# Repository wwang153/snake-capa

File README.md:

# snake-capa
 This is the sub directory for BIGSS Snake Tool ROS2 Description.

Access Link below:

https://github.com/jhu-bigss/CDM_Capacitive_Shape_Sensing_ROS2

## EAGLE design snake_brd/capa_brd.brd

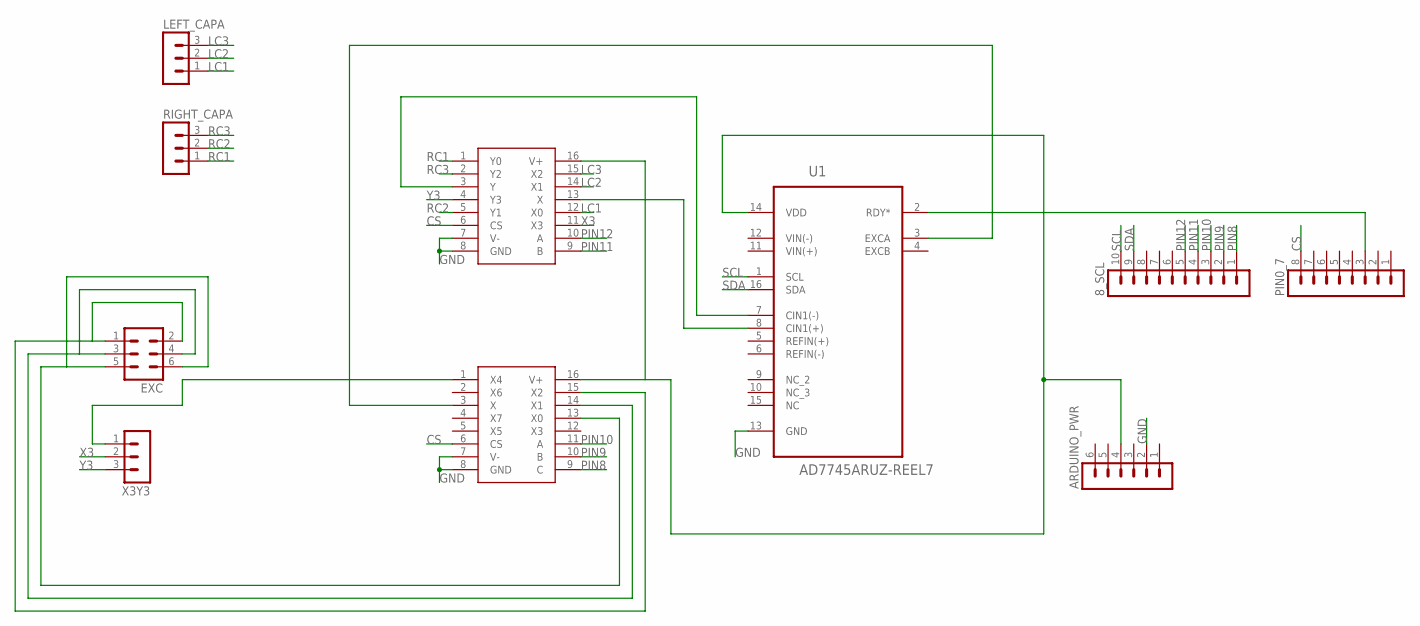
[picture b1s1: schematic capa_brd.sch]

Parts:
8_SCL: MA10-1
ARDUINO_PWR: MA06-1
EXC: MA03-2
LEFT_CAPA: MA03-1
PIN0_7: MA08-1
RIGHT_CAPA: MA03-1
U1: AD7745ARUZ-REEL7; SOP65P640X120-16N
U$1: DG4051E
U$2: DG4052E
X3Y3: MA03-1

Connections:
CS: PIN0_7.8, U$1.6 (CS), U$2.6 (CS)
GND: ARDUINO_PWR.2, U1.13 (GND), U$1.7 (V-), U$1.8 (GND), U$2.7 (V-), U$2.8 (GND)
LC1: LEFT_CAPA.1, U$2.12 (X0)
LC2: LEFT_CAPA.2, U$2.14 (X1)
LC3: LEFT_CAPA.3, U$2.15 (X2)
unnamed: U1.8 (CIN1(+)), U$2.13 (X)
unnamed: U1.7 (CIN1(-)), U$2.3 (Y)
unnamed: U1.3 (EXCA), U$1.3 (X)
unnamed: EXC.5, EXC.6, U$1.13 (X0)
unnamed: EXC.3, EXC.4, U$1.14 (X1)
unnamed: EXC.1, EXC.2, U$1.15 (X2)
unnamed: PIN0_7.3, U1.2 (RDY*)
unnamed: ARDUINO_PWR.4, U1.14 (VDD), U$1.16 (V+), U$2.16 (V+)
unnamed: U$1.1 (X4), X3Y3.1
PIN8: 8_SCL.1, U$1.9 (C)
PIN9: 8_SCL.2, U$1.10 (B)
PIN10: 8_SCL.3, U$1.11 (A)
PIN11: 8_SCL.4, U$2.9 (B)
PIN12: 8_SCL.5, U$2.10 (A)
RC1: RIGHT_CAPA.1, U$2.1 (Y0)
RC2: RIGHT_CAPA.2, U$2.5 (Y1)
RC3: RIGHT_CAPA.3, U$2.2 (Y2)
SCL: 8_SCL.10, U1.1 (SCL)
SDA: 8_SCL.9, U1.16 (SDA)
X3: U$2.11 (X3), X3Y3.2
Y3: U$2.4 (Y3), X3Y3.3

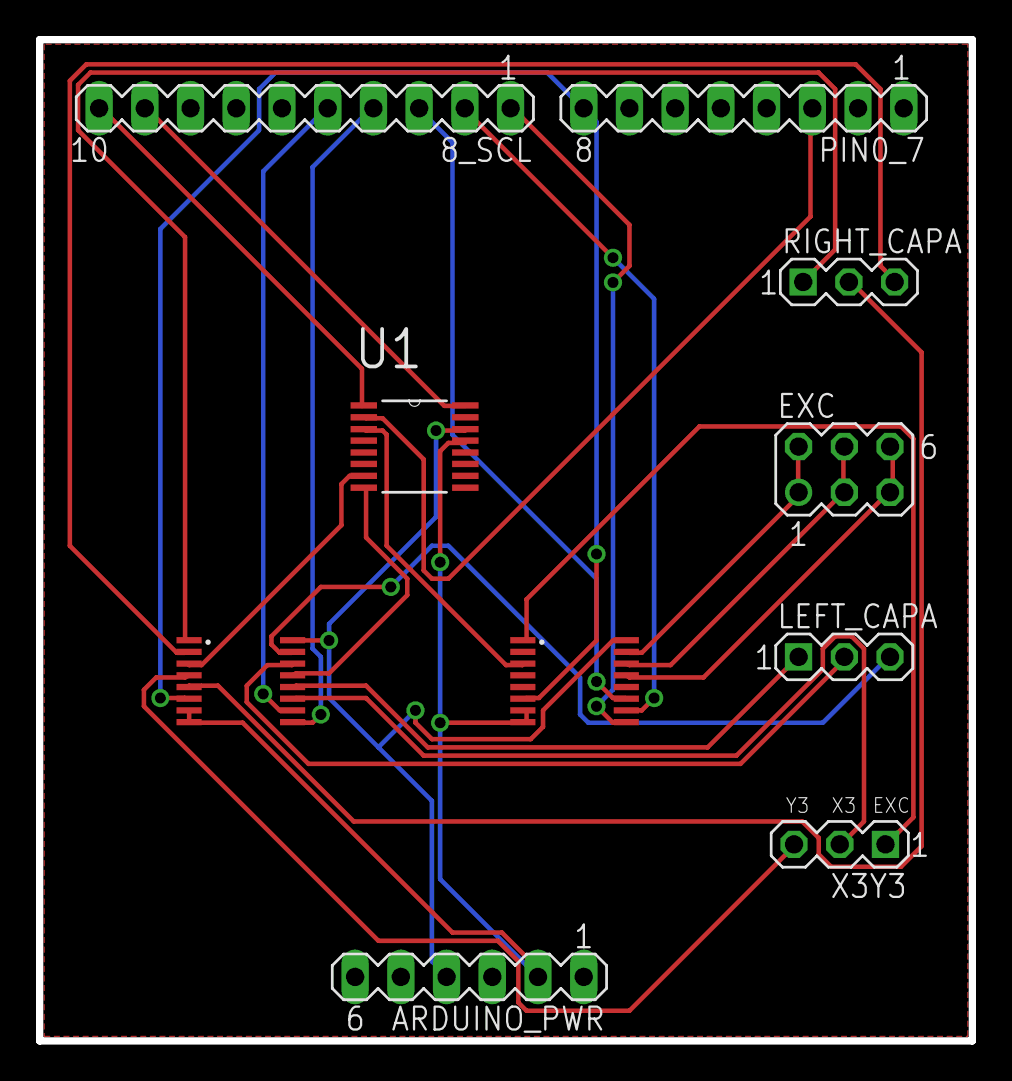
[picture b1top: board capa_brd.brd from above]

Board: 2 copper layers, 51.8 x 55.6 mm, 10 parts (0 on the bottom side), 26 nets.

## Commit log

2022-06-21 arduino code change
    changed for serial read in python.
2022-06-27 encoder test code indluded
    added encoder test code, and delete the not needed py plot directory created before.
2022-06-28 Update encoder_test.ino
    added second encoder to the code
2022-06-28 py file used to get sample data from 2 COM ports
    read and generate CSV file from 2 arduino.
2022-06-29 Update encoder_test.ino
    get correct form for py sample code.
2022-06-29 add gitignore
2022-06-29 remove .txt from .gitignore.txt
2022-06-29 50 samples write to CSV.
2022-06-30 Update encoder_test.ino
    add accommodation for encoder drifting.
2022-06-30 Update main.py
    added sample frequency.
2022-06-30 Update main.py
    accommodate the issue introduced by pyserial read buffer, and update the output file with encoder value.
2022-06-30 remove button ISR.
    remove button ISR
2022-07-06 Change AD7745 read frequency + arduino shield PCB included.
2022-08-02 Update for the AD7747 differential sensing.
2022-08-03 Remove the 7747 testing comments.
2022-08-11 Changes for 7747 sampling and main functions.
2022-08-12 Collecting data changes.
2022-09-29 Add I2C multiplexer.
2022-09-29 add I2C arduino interrupt
2022-10-06 Add single conversion for AD7747.
2022-10-06 Add single_conversion and remove dup
2022-11-02 Added arduino for single conversion.
2023-01-04 Adjust COM port
